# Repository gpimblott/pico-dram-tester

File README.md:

# Pico DRAM Tester

Having trouble with your old-school DIP dynamic RAM chips? Here's a simple
RAM tester that will give you a definitive pass or fail for a variety of
chips.

**This is an updated version with additional tests and refaftoring of the code.
Based on the early beta release by schlae . The software is not completed. Feel free to
build a tester and try it out, and submit bug reports.**

Benefits

* Tests RAM *at full speed* so you can feel confident about a chip that passes.
* Easy to construct with widely-available parts. No surface mount chips.
* Low cost
* Built-in DC-DC modules generate extra voltages required by 4116-class chips
* Can be operated from a bench supply for voltage margin testing

Supported Devices

* 4027 (4K x 1)
* 4108 (8K x 1 that are 4116s with only half test good: MK4108, TMS4108, etc)
* 4116 (16K x 1)
* 4132 (32K x 1, piggyback)
* 4132 (32K x 1 that are 4164s with only half tested good: TMS4532, M3732)
* 4164 (64K x 1)
* 41128 (128K x 1, piggyback)
* 41256 (256K x 1)
* 4416 (16K x 4)
* 4464 (64K x 4)
* 44256 (256K x 4)

Out of scope

* SRAM, DRAM chips larger than 1MBit
* Logic chips

## Versions
* 0.1 - Beta version designed and coded by schlae (@tubetime)
* 0.2 - Changed to higher voltage as recommended by schlae in notes below.
* 0.3 - Restructure code by G.Pimblott and merged in board changes for DC Jack by Markeno76
* 0.4 - Added Checkerboard test
* 0.5 - Added Address error test

## Construction

Revision 2.2 adds a DC Barrel Jack option.  
It also adds solder jumper pads to allow use of the original Panasonic Encoder
or the common Generic Encoders.

[Fab package](fab/pico-dram-tester-rev2.zip)

[Schematic](pico-dram-tester.pdf)

[Bill of Materials](pico-dram-tester.csv)

The board is a simple 2-layer board, 100mm x 100mm, and 1.6mm thick. Fabricate
at your favorite vendor in any color you wish.

You may populate the board only with the sockets for devices you plan to use,
or you may populate all the sockets. You can try substituting the sockets with
standard IC sockets, but I recommend ZIF sockets which are much easier to use.
Why so many sockets? It saves you from having to install dozens of pin control
transistors required to make a tester work with a single universal socket.

Populate Q1, U7, U8, R2, R3, R4, and R5 if you would like to test 4116 and
4132 devices without requiring an external -5V and +12V power supply.

If you want to provide the -5V, +5V, and +12V power from your bench supply,
then you may leave those components off of the board and connect your power
leads to the -5V, +5V, and +12V test points. If you don't plan to test 4116
or 4132 chips, then you can safely leave out those components.

The LCD display is nominally the [Adafruit 4383](https://www.adafruit.com/product/4383) which is to be installed at location J1 (U9 is not required when using
this display). You can also use cheaper devices available from Aliexpress and
others. They are 8-pin LCD displays sold as 1.14" 135x240 IPS ST7789 modules.
Install this display at position J2. You may also need to add the voltage
monitor at position U9.

For several reasons, this board requires a Pico 2 microcontroller board and
will not work at all with the Pico 1.

After installing all the components and inspecting the board for accidental
short circuits, connect the Pico 2 via the USB connector to a computer. The
device should power up and appear as a USB mass storage device. Copy the
prebuilt firmware file [pmemtest.uf2](firmware/pmemtest.uf2) to this device, and the Pico 2 will
program itself. Reset the power and you should see a menu of chips on the LCD
screen.

## Using the DRAM Tester

Before starting, connect the tester to a power source:

* If you did not install U7 and U8, connect a bench supply to the GND, -5V, +5V, and +12V test points. Connect the Pico 2 USB jack to a power adapter or computer.
* If you installed U7 and U8, connect a 5V bench supply to the 5VIN and GND test points. Instead of a bench supply, you could connect the Pico 2 USB jack to a power adapter, but you won't be able to control the voltage. A computer often has a much lower voltage and you may fail RAM chips that actually function at 5V.

1. Install the chip in the socket designated for that type of memory chip, following the pin 1 orientation (the pin 1 notch faces the ZIF socket lever). Note that some of the sockets are used for several types of memory.
2. Rotate the selection knob until the correct part number is highlighted, and push down on the top of the selection knob (it's also a button!)
3. If you make a mistake, press the button to the left of the selection knob to go back.
4. After selecting a part, you need to pick the correct speed grade to run the
test. Often the speed grade is marked on the chip as a suffix. For example, -15
typically means 150ns. If you're not sure, pick the slowest speed.
5. If you are using an external bench power supply to supply -5V and +12V, turn it on now. If you soldered in the on-board voltage converter modules, you don't need to do anything. Push the top of the selection knob to continue.
6. The test runs. You will see a red "X" if the test fails or a green checkmark if the test passes.
7. You can rerun the test immediately by pushing down on the top of the selection knob. Or go back to the menu by pushing the button to the left.

Note: The visualization pane on the left is just for entertainment and doesn't
really represent bad bits.

## Technical Details

The Pico 2 microcontroller (RP2350) has built-in high-speed PIO processors
which are overclocked to 300MHz. This means that the DRAM timing can be set
to a resolution of 3.3ns. The RAM test runs on the second CPU core, decoupling
it from the GUI, which runs on the first CPU core.

RAM testing can be surprisingly complicated. There are many kinds of failures:

* Stuck-at fault - a cell is stuck at a 1 or a 0
* Stuck-open fault - a cell isn't connected (input or output)
* Transition fault - a cell can't go from one state to another (1 to 0 or 0 to 1)
* Data retention fault - a cell flips after a time delay
* Coupling fault - the state of one cell affects the state of another
* Neighborhood pattern sensitive fault - a specific pattern in nearby cells causes a cell to flip
* Address decoder fault - cells may be isolated, or multiple cells accessed at the same address, or multiple addresses may access a single cell

There are a number of "traditional" RAM tests such as the checkerboard or
walking 1/0, but these tests can be slow and don't have precise coverage over
all failure modes. The Pico DRAM Tester uses more modern testing algorithms:

* March-B. This is a sequence of linear reads and writes designed to catch address faults, stuck-at faults, transition faults, and coupling faults.
* Pseudorandom test. This test loads a pseudorandom number sequence into the memory, reads it back, and checks to make sure it didn't change. The test is repeated with 64 different pseudorandom patterns to enhance coverage. The patterns are identical between runs, making the test repeatable. The test only uses pseudorandom data and does not randomize the address. This test can detect many pattern-sensitive faults.
* Refresh test. This test loads a pattern into the memory, waits for a time delay, and then tries to read it back. The time delay is longer than a typical refresh rate. This test can detect data retention faults.

## Known Issues

* The 41128 test is not yet reliable.

## Troubleshooting

Check your solder connections. Does the Pico 2 board show up in bootloader mode when you plug it into a computer?

The Pico DRAM Tester uses an overclocked Pico 2 configuration.
Some Pico 2 boards may not work well at 300MHz, crashing or not drawing the GUI on the screen correctly.
You may be able to get it working by editing pmemtest.c, find the line `vreg_set_voltage(VREG_VOLTAGE_1_15);` and change the voltage setting to `VREG_VOLTAGE_1_20`.

## License

This work is licensed under a Creative Commons Attribution-ShareAlike 4.0
International License. See [https://creativecommons.org/licenses/by-sa/4.0/](https://creativecommons.org/licenses/by-sa/4.0/).

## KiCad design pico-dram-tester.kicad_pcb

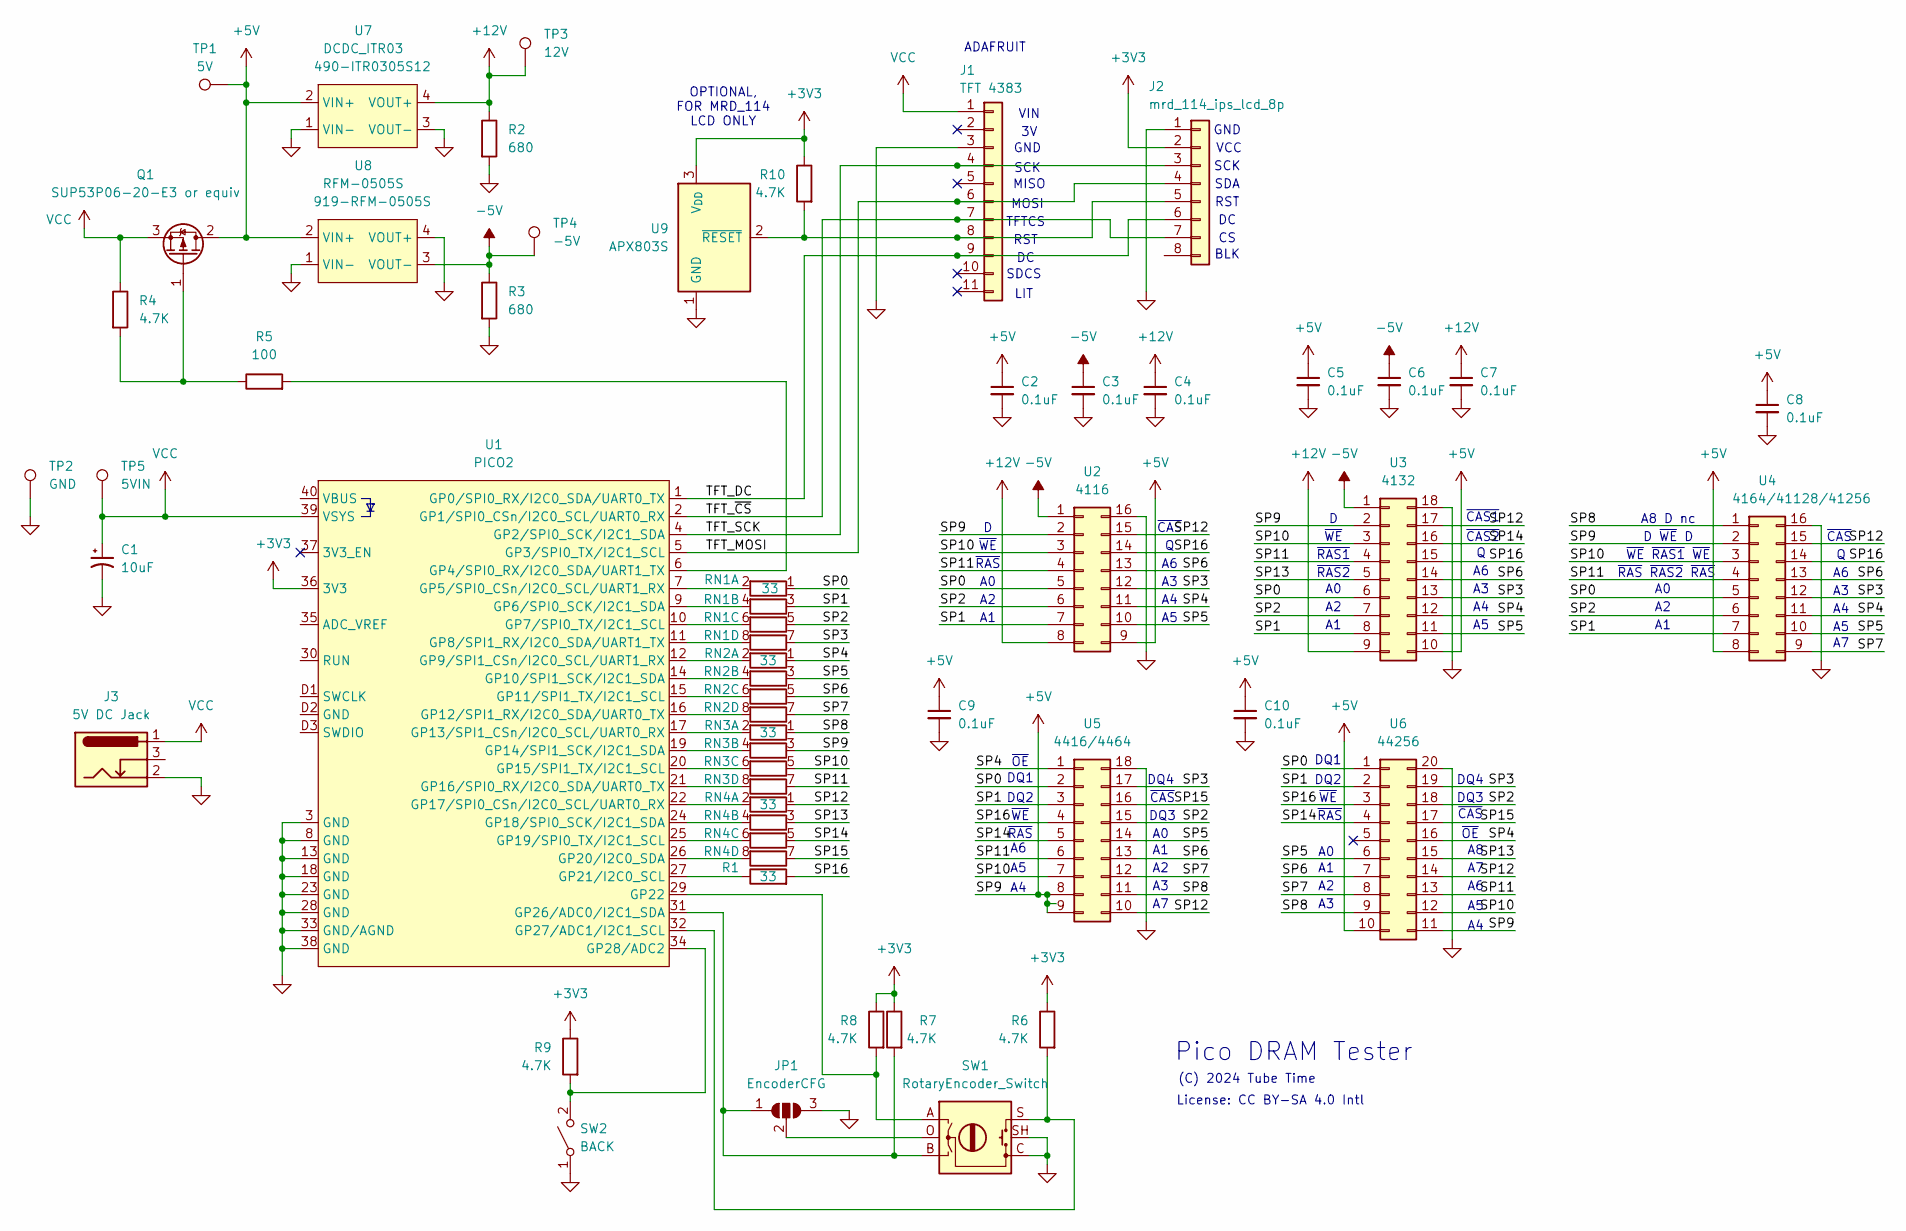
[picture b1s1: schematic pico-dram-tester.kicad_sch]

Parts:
C1: 10uF; CAPAE200P500X1100; Mouser 667-ECA-1VM100
C2, C3, C4, C5, C6, C7, C8, C9, C10: 0.1uF; CAPAC200; Mouser 80-C322C104M5U
J1: TFT 4383; ADAFRUIT_4383
J2: mrd_114_ips_lcd_8p; PinHeader_1x08_P2.54mm_Vertical
J3: 5V DC Jack; BarrelJack_Horizontal
JP1: EncoderCFG; SolderJumper-3_P1.3mm_Open_Pad1.0x1.5mm
Q1: SUP53P06-20-E3 or equiv; TO-220-3_Vertical; Mouser 781-SUP53P06-20-E3
R1: 33; RESA500; Mouser 594-MBB02070C3309FCT
R2, R3: 680; RESA500; Mouser 594-MBB02070C6800FCT
R4, R6, R7, R8, R9, R10: 4.7K; RESA500; Mouser 594-MBB02070C4701FCT
R5: 100; RESA500; Mouser 594-MBB02070C1000FCT
RN1, RN2, RN3, RN4: 33; R_Array_SIP8; Mouser 652-4608X-2LF-33
SW1: RotaryEncoder_Switch; PANASONIC_EVEY; Mouser 667-EVE-YBCAJO16B
SW2: BACK; SW_SPST_Omron_B3F-50xx; Mouser 653-B3F-4005
TP1: 5V; TestPoint_Keystone_5005-5009_Compact; Mouser 534-5005
TP2: GND; TestPoint_Keystone_5005-5009_Compact; Mouser 534-5006
TP3: 12V; TestPoint_Keystone_5005-5009_Compact; Mouser 534-5009
TP4: -5V; TestPoint_Keystone_5005-5009_Compact; Mouser 534-5007
TP5: 5VIN; TestPoint_Keystone_5005-5009_Compact; Mouser 534-5005
U1: PICO2; Pico2; Mouser 358-SC1631
U2: 4116; DIP_Socket-16_W4.3_W5.08_W7.62_W10.16_W10.9_3M_216-3340-00-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
U3: 4132; DIP_Socket-18_W4.3_W5.08_W7.62_W10.16_W10.9_3M_218-3341-00-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
U4: 4164/41128/41256; DIP_Socket-16_W4.3_W5.08_W7.62_W10.16_W10.9_3M_216-3340-00-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
U5: 4416/4464; DIP_Socket-18_W4.3_W5.08_W7.62_W10.16_W10.9_3M_218-3341-00-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
U6: 44256; DIP_Socket-20_W4.3_W5.08_W7.62_W10.16_W10.9_3M_220-3342-00-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
U7: DCDC_ITR03; Mouser 490-ITR0305S12
U8: RFM-0505S; DCDC_ITR03; Mouser 919-RFM-0505S
U9: APX803S; SOT-23_Handsoldering; Mouser 621-APX803S-29SA-7

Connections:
+3V3: J2.2, R6.1, R7.1, R8.1, R9.1, R10.1, U1.36 (3V3), U9.3 (V_{DD})
+5V: C2.1, C5.1, C8.1, C9.1, C10.1, Q1.2 (D), RN3.3 (R2.1), TP1.1, U2.2, U2.9, U3.2, U3.10, U4.2, U4.8, U5.8, U5.9, U6.10, U6.11, U7.2 (VIN+), U8.2 (VIN+)
+12V: C4.1, C7.1, R2.1, TP3.1, U2.8, U3.9, U7.4 (VOUT+)
-5V: C3.1, C6.1, R3.1, TP4.1, U2.1, U3.1, U8.3 (VOUT-)
/SP0: RN1.1 (R1.1), U2.5, U3.6, U4.5, U5.2, U6.1
/SP1: RN1.3 (R2.1), U2.7, U3.8, U4.7, U5.3, U6.2
/SP2: RN1.5 (R3.1), U2.6, U3.7, U4.6, U5.15, U6.18
/SP3: RN1.7 (R4.1), U2.12, U3.13, U4.12, U5.17, U6.19
/SP4: RN2.1 (R1.1), U2.11, U3.12, U4.11, U5.1, U6.16
/SP5: RN2.3 (R2.1), U2.10, U3.11, U4.10, U5.14, U6.6
/SP6: RN2.5 (R3.1), U2.13, U3.14, U4.13, U5.13, U6.7
/SP7: RN2.7 (R4.1), U4.9, U5.12, U6.8
/SP8: RN3.1 (R1.1), U4.1, U5.11, U6.9
/SP10: RN3.5 (R3.1), U2.3, U3.3, U4.3, U5.7, U6.12
/SP11: RN3.7 (R4.1), U2.4, U3.4, U4.4, U5.6, U6.13
/SP12: RN4.1 (R1.1), U2.15, U3.17, U4.15, U5.10, U6.14
/SP13: RN4.3 (R2.1), U3.5, U6.15
/SP14: RN4.5 (R3.1), U3.16, U5.5, U6.4
/SP15: RN4.7 (R4.1), U5.16, U6.17
/SP16: R1.2, U2.14, U3.15, U4.14, U5.4, U6.3
/TFT_DC: J1.9, J2.6, U1.1 (GP0/SPI0_RX/I2C0_SDA/UART0_TX)
/TFT_MOSI: J1.6, J2.4, U1.5 (GP3/SPI0_TX/I2C1_SCL)
/TFT_SCK: J1.4, J2.3, U1.4 (GP2/SPI0_SCK/I2C1_SDA)
/TFT_~CS: J1.7, J2.7, U1.2 (GP1/SPI0_CSn/I2C0_SCL/UART0_RX)
GND: C1.2, C2.2, C3.2, C4.2, C5.2, C6.2, C7.2, C8.2, C9.2, C10.2, J1.3, J2.1, J3.2, JP1.3 (B), R2.2, R3.2, SW1.C, SW1.SH, SW2.1 (A), TP2.1, U1.3 (GND), U1.8 (GND), U1.13 (GND), U1.18 (GND), U1.23 (GND), U1.28 (GND), U1.33 (GND/AGND), U1.38 (GND), U2.16, U3.18, U4.16, U5.18, U6.20, U7.1 (VIN-), U7.3 (VOUT-), U8.1 (VIN-), U8.4 (VOUT+), U9.1 (GND)
unnamed: J1.8, J2.5, R10.2, U9.2 (~RESET)
unnamed: JP1.1 (A), R7.2, SW1.B, U1.31 (GP26/ADC0/I2C1_SDA)
unnamed: JP1.2 (C), SW1.O
unnamed: Q1.1 (G), R4.2, R5.1
unnamed: RN1.2 (R1.2), U1.7 (GP5/SPI0_CSn/I2C0_SCL/UART1_RX)
unnamed: RN1.4 (R2.2), U1.9 (GP6/SPI0_SCK/I2C1_SDA)
unnamed: RN1.6 (R3.2), U1.10 (GP7/SPI0_TX/I2C1_SCL)
unnamed: RN1.8 (R4.2), U1.11 (GP8/SPI1_RX/I2C0_SDA/UART1_TX)
unnamed: RN2.2 (R1.2), U1.12 (GP9/SPI1_CSn/I2C0_SCL/UART1_RX)
unnamed: RN2.4 (R2.2), U1.14 (GP10/SPI1_SCK/I2C1_SDA)
unnamed: RN2.6 (R3.2), U1.15 (GP11/SPI1_TX/I2C1_SCL)
unnamed: RN2.8 (R4.2), U1.16 (GP12/SPI1_RX/I2C0_SDA/UART0_TX)
unnamed: RN3.2 (R1.2), U1.17 (GP13/SPI1_CSn/I2C0_SCL/UART0_RX)
unnamed: RN3.4 (R2.2), U1.19 (GP14/SPI1_SCK/I2C1_SDA)
unnamed: RN3.6 (R3.2), U1.20 (GP15/SPI1_TX/I2C1_SCL)
unnamed: RN3.8 (R4.2), U1.21 (GP16/SPI0_RX/I2C0_SDA/UART0_TX)
unnamed: RN4.2 (R1.2), U1.22 (GP17/SPI0_CSn/I2C0_SCL/UART0_RX)
unnamed: RN4.4 (R2.2), U1.24 (GP18/SPI0_SCK/I2C1_SDA)
unnamed: RN4.6 (R3.2), U1.25 (GP19/SPI0_TX/I2C1_SCL)
unnamed: RN4.8 (R4.2), U1.26 (GP20/I2C0_SDA)
unnamed: R9.2, SW2.2 (B), U1.34 (GP28/ADC2)
unnamed: R5.2, U1.6 (GP4/SPI0_RX/I2C0_SDA/UART1_TX)
unnamed: R1.1, U1.27 (GP21/I2C0_SCL)
unnamed: R8.2, SW1.A, U1.29 (GP22)
unnamed: R6.2, SW1.S, U1.32 (GP27/ADC1/I2C1_SCL)
VCC: C1.1, J1.1, J3.1, Q1.3 (S), R4.1, TP5.1, U1.39 (VSYS)

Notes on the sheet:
~{OE}
~{CAS}
~{RAS}
ADAFRUIT
GND
BLK
LIT
~{WE}
~{CAS2}
~{CAS1}
License: CC BY-SA 4.0 Intl
MOSI
DQ2
SDCS
(C) 2024 Tube Time
DQ3
~{RAS} ~{RAS2} ~{RAS}
OPTIONAL, FOR MRD_114 LCD ONLY
A8 D nc
DQ1
TFTCS
DQ4
SCK
~{RAS1}
~{RAS2}
VIN
SDA
VCC
Pico DRAM Tester
D ~{WE} D
~{WE} ~{RAS1} ~{WE}
RST
MISO

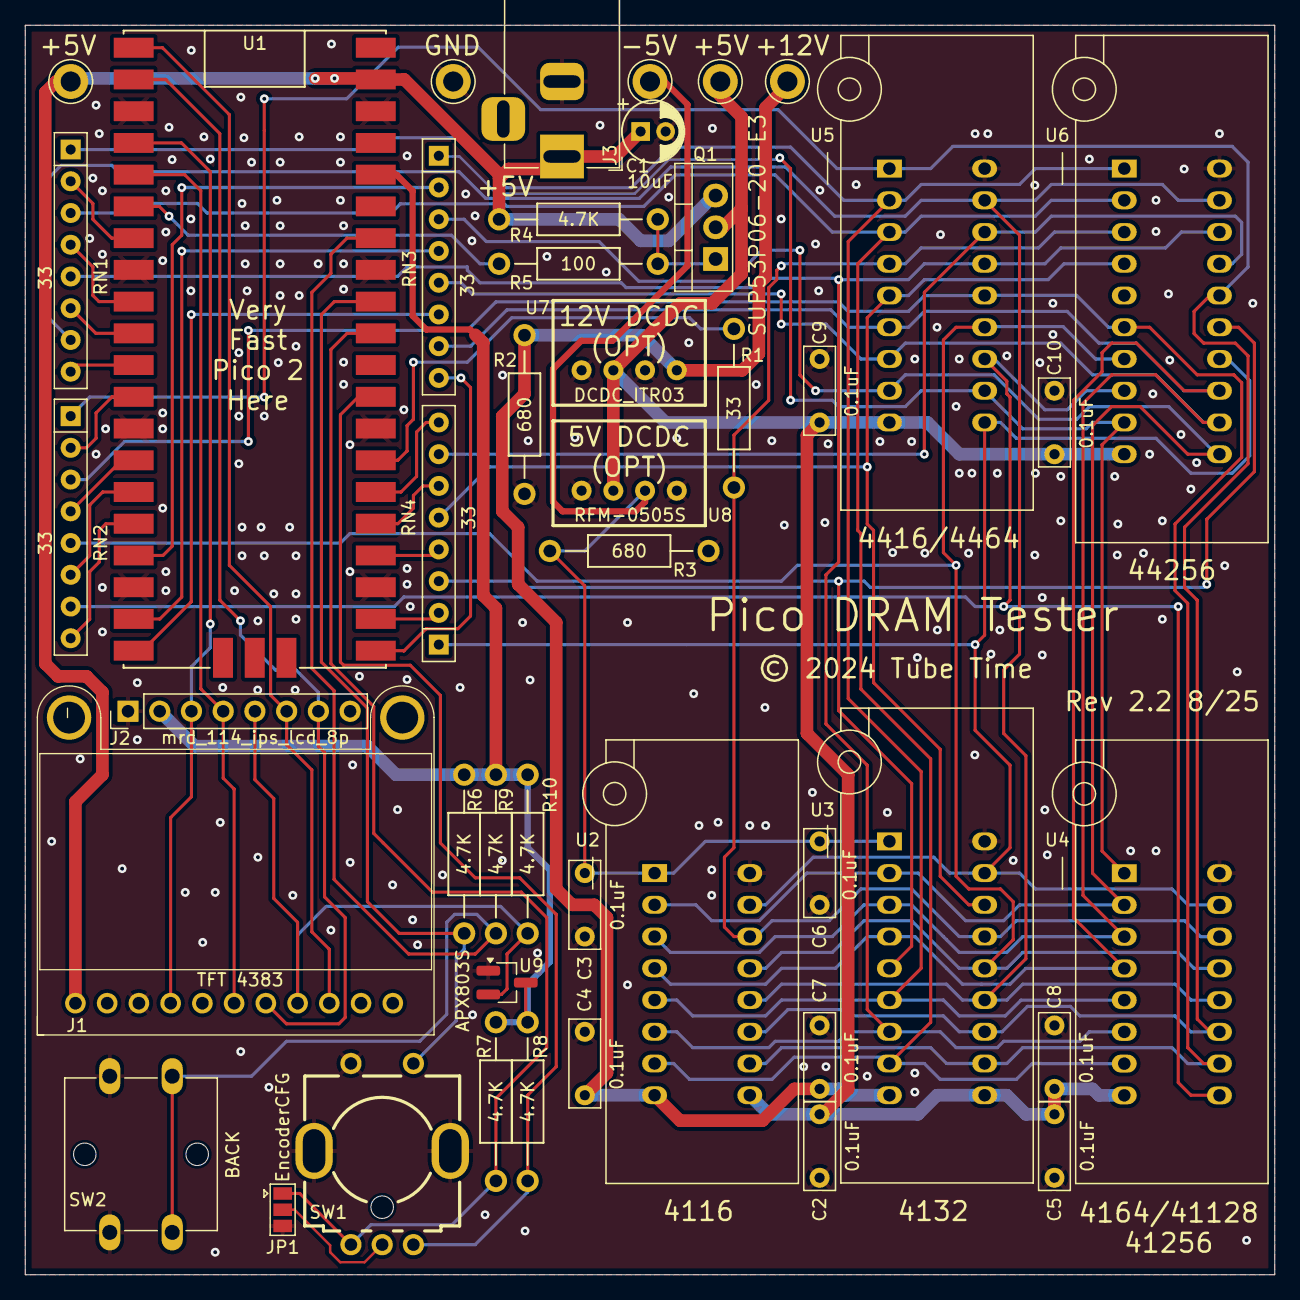
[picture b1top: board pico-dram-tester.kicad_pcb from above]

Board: 2 copper layers, 100.0 x 100.0 mm, 45 parts (0 on the bottom side), 51 nets.

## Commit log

2024-09-26 Get rid of autopull for now
2024-09-29 Add fast page and read
2024-10-01 RAM read and write functions
2024-10-01 Read data bit
2024-10-02 Fix FIFO issue
2024-10-02 overclock, update timings to 150ns
2024-10-03 Create new firmware directory
2024-10-03 Initial marchb test
2024-10-11 initial st7789 display init code
2024-10-11 clear screen, draw line
2024-10-12 tweaks to st7789 driver
2024-10-12 bitblt added
2024-10-17 initial proportional font support
2024-10-17 add bold mode
2024-10-18 dialog elements
2024-10-18 support for multiple fonts
2024-10-18 scrollbars
2024-10-22 first PCB fab
2024-10-25 button and quadrature encoder
2024-10-25 scrollbar code
2024-10-25 Add support for ICO files
2024-10-25 Add text box, message dialog
2024-10-25 RAM test interface
2024-10-26 first working end-to-end DRAM test!
2024-10-28 initial visualization
2024-10-28 icon_support now handles multiple icons per file
2024-10-28 add some icons
2024-10-28 Fix icon color swap
2024-10-28 test status improvements
2024-10-29 Fix PIO allocation leak
2024-10-29 add time delay patching
2024-10-30 abstract ram chip stuff away
2024-10-30 Add remaining 4164 timings
2024-10-31 Correct 4164 timings
2024-10-31 Refactor pio in prep for more chips
2024-11-01 add 4116 support
2024-11-01 add 41256 support
2024-11-01 Fix animation glitch
2024-11-05 Layout corrections
2024-11-18 initial 44256 partially functional
2024-11-18 41256 timing tweak for 100ns
2024-11-18 prevent list box out of range
2024-11-19 timing adjustments to 44256
2024-11-19 Working 44256 test
2024-11-19 41256 turn off input sync
2024-11-20 More listbox fixes
2024-11-20 Add 4416 and 4464
2024-11-20 fix 4416/4464 timing
2024-11-21 rename 4-bit memory pio
2024-11-21 initial 41128 support
2024-11-28 Add 4132 support
2024-11-28 fix timing patch bug, fix 4416 address, 44256 timing
2024-12-02 improve visualizations
2024-12-02 add pseudorandom test
2024-12-02 initial version of refresh test
2024-12-03 adjust 41128 timings
2024-12-03 more pseudorandom numbers
2024-12-04 add early prebuilt uf2
2024-12-04 Add readme and new fab package
2024-12-04 Header comment cleanup
2025-01-11 Added 3D_files, updated BOM
2025-01-13 increase vcore slightly for better overclock
2025-03-31 add 300ns timing to 4164
2025-06-02 Update MOSFET Q1, fix R1 part number
2025-08-02 DCJack and Generic Encoder
    Added DC Barrel Jack. Added Configuration Jumper pads to use the common Generic Encoder
2025-08-02 ImagesAdded
2025-08-03 Fix: ps and refresh tests no longer write all '1'
2025-08-05 Fix back button bug
2025-08-07 Add 4132s that are half-qualified 4164 chips
2025-08-07 Update readme with instructions and 4132
2025-08-07 Add support for 4108
2025-08-07 Add 4027. Fix missing menu items.
2025-08-07 Add RAS initialization after powerup
2025-08-27 Add 4408 support. Fix debounce.
2025-09-24 Increase the voltage to work with my board
2025-09-24 Build files
2025-09-25 Refactored code to allow easier development
2025-09-25 Update built firmare
2025-09-26 Create c-cpp.yml
    Pico build action
2025-09-26 Splash screen and commenting code
2025-09-26 splash screen
2025-09-26 Fixed memory read/write error in test
2025-09-26 set the voltage to 1.25v
2025-09-26 Added checkerboard test
2025-09-26 Update version number
2025-09-26 Add checkerboard test
2025-09-26 Add checkerboard
2025-09-27 update splash screen
2025-09-27 Changed the splsh screen colours
2025-09-27 Update README.md
    Added initial 0.4 notes
2025-09-28 Reset voltage to see if it helps stability
2025-09-28 Update checkerboard visualisation for 4 bit 256K chips
2025-09-28 Update checkerboard visualisation and execution
2025-09-28 Ensure that the cores are reset after an SWD flash - might not help
2025-09-28 Updated to allow the sensitivity of the rotary encder to set easily
2025-09-28 Rotary encoder sensitivty
2025-09-28 Initial skeleton for 2114 chips
2025-09-28 Initial code changes for 2114 sram
2025-10-01 Remove 2114
2025-10-01 Add copilot instructucions
2025-10-06 More updates
2025-10-06 Updated version number and documentation
2025-10-06 Removed unused/missing header

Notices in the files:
pico-dram-tester.kicad_pcb:
© 2024 Tube Time
